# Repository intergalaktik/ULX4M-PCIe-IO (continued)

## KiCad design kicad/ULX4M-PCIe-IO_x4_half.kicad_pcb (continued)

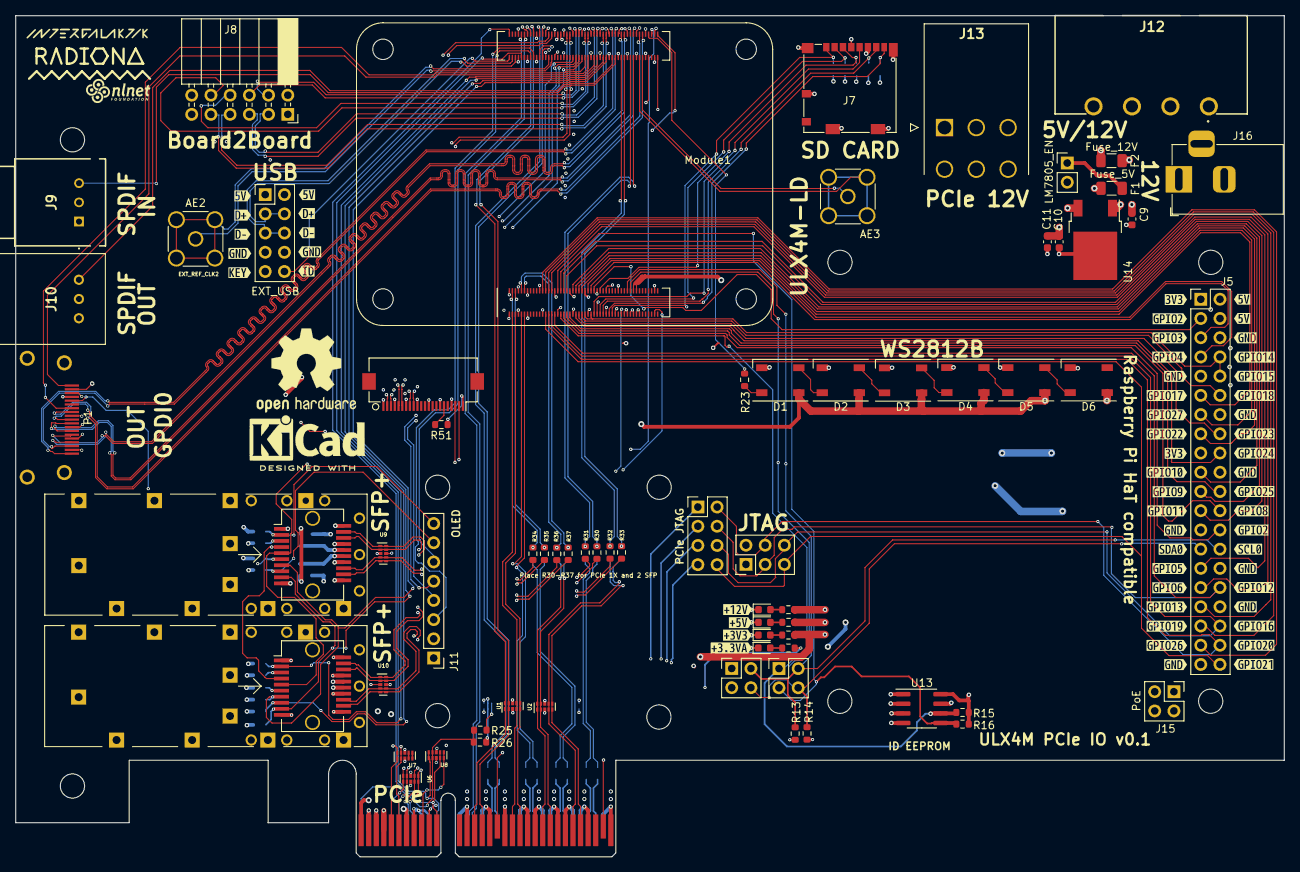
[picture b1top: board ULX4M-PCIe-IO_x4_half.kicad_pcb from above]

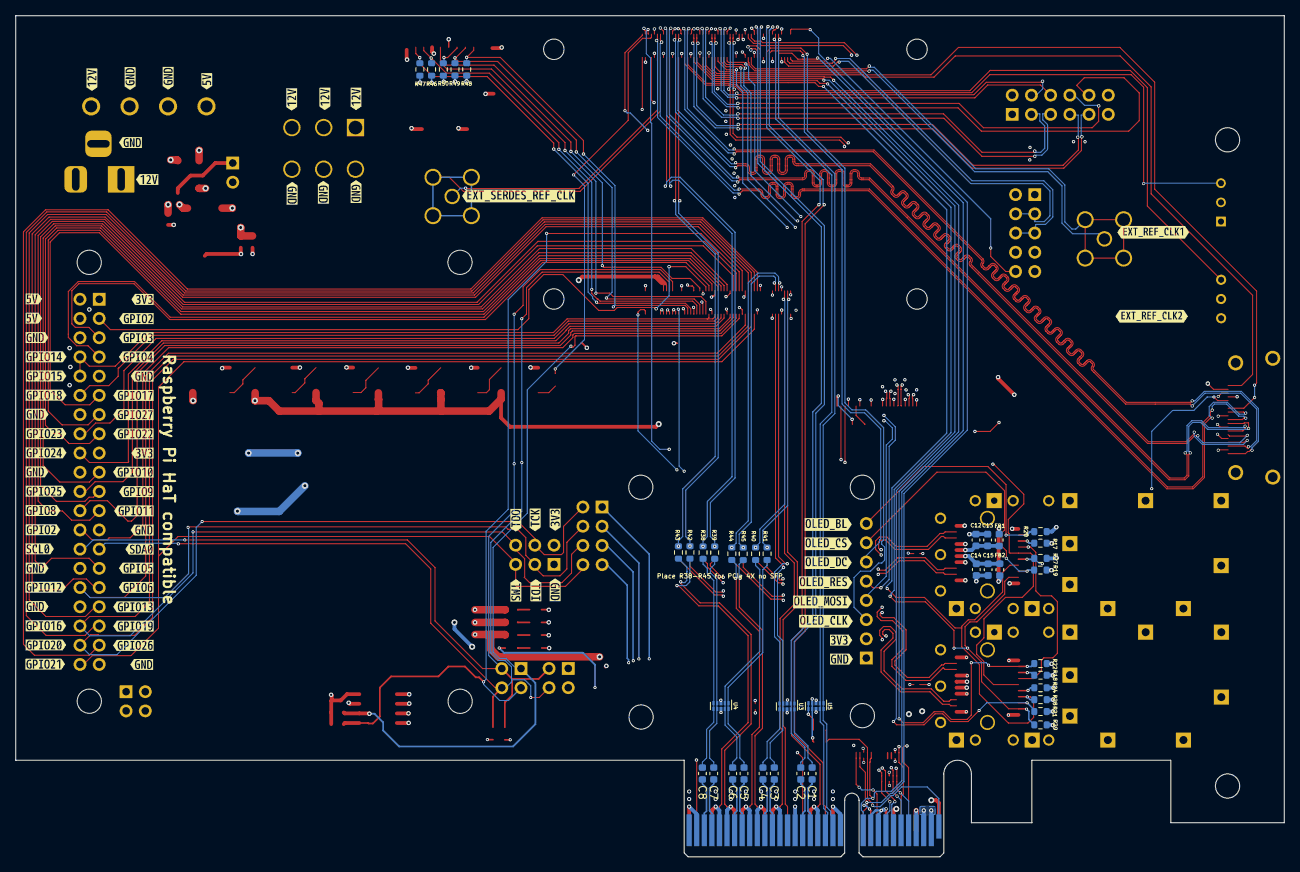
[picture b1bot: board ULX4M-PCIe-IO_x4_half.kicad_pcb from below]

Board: 6 copper layers, 167.7 x 111.2 mm, 241 parts (109 on the bottom side), 161 nets.

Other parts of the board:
kibuzzard-66C31A8D: G***; kibuzzard-66C31A8D
kibuzzard-66C31AAA: G***; kibuzzard-66C31AAA
kibuzzard-63524D1: G***; kibuzzard-63524D95
kibuzzard-63524E7F12: G***; kibuzzard-63524E7F
kibuzzard-63524EC5: G***; kibuzzard-63524EC5
kibuzzard-63524ECE: G***; kibuzzard-63524ECE
kibuzzard-63524ED4: G***; kibuzzard-63524ED4
kibuzzard-63524EDC: G***; kibuzzard-63524EDC
kibuzzard-63524EE2: G***; kibuzzard-63524EE2
kibuzzard-63524EEA: G***; kibuzzard-63524EEA
kibuzzard-63524EF7: G***; kibuzzard-63524EF7
kibuzzard-63524EFF: G***; kibuzzard-63524EFF
kibuzzard-63524F4A: G***; kibuzzard-63524F4A
kibuzzard-63524F4F: G***; kibuzzard-63524F4F
kibuzzard-63524F5B: G***; kibuzzard-63524F5B
kibuzzard-63524F6E: G***; kibuzzard-63524F6E
kibuzzard-63524F8C: G***; kibuzzard-63524F8C
kibuzzard-63524F9F: G***; kibuzzard-63524F9F
kibuzzard-63524F11: G***; kibuzzard-63524F11
kibuzzard-63524F17: G***; kibuzzard-63524F17
kibuzzard-63524F21: G***; kibuzzard-63524F21
kibuzzard-63524F28: G***; kibuzzard-63524F28
kibuzzard-63524F31: G***; kibuzzard-63524F31
kibuzzard-63524F38: G***; kibuzzard-63524F38
kibuzzard-63524F40: G***; kibuzzard-63524F40
kibuzzard-63524F45: G***; kibuzzard-63524F45
kibuzzard-63524F57: G***; kibuzzard-63524F57
kibuzzard-63524F60: G***; kibuzzard-63524F60
kibuzzard-63524F75: G***; kibuzzard-63524F75
kibuzzard-63524F84: G***; kibuzzard-63524F84
kibuzzard-63524F92: G***; kibuzzard-63524F92
kibuzzard-63524F99: G***; kibuzzard-63524F99
kibuzzard-63524FA8: G***; kibuzzard-63524FA8
kibuzzard-63524FAF: G***; kibuzzard-63524FAF
kibuzzard-63524FB4: G***; kibuzzard-63524FB4
kibuzzard-63524FBB: G***; kibuzzard-63524FBB
kibuzzard-63524FC2: G***; kibuzzard-63524FC2
kibuzzard-63524FC9: G***; kibuzzard-63524FC9
kibuzzard-63524FCF: G***; kibuzzard-63524FCF
kibuzzard-63524FD4: G***; kibuzzard-63524FD4
kibuzzard-63524FDC: G***; kibuzzard-63524FDC
kibuzzard-63524FE4: G***; kibuzzard-63524FE4
kibuzzard-63525A7A: G***; kibuzzard-63525A7A
kibuzzard-63525A8D: G***; kibuzzard-63525A8D
kibuzzard-63525A73: G***; kibuzzard-63525A73
kibuzzard-63525A80: G***; kibuzzard-63525A80
kibuzzard-63525A86: G***; kibuzzard-63525A86
kibuzzard-63525A94: G***; kibuzzard-63525A94
kibuzzard-63525AA1: G***; kibuzzard-63525AA1
kibuzzard-63525AA7: G***; kibuzzard-63525AA7
kibuzzard-63525BEB: G***; kibuzzard-63525BEB
kibuzzard-63525C1D: G***; kibuzzard-63525C1D
kibuzzard-63525C11: G***; kibuzzard-63525C11
kibuzzard-63525C35: G***; kibuzzard-63525C35
kibuzzard-63525FEA: G***; kibuzzard-63525FEA
kibuzzard-635253B6: G***; kibuzzard-635253B6
kibuzzard-635253BD: G***; kibuzzard-635253BD
kibuzzard-635253C7: G***; kibuzzard-635253C7
kibuzzard-635253DB: G***; kibuzzard-635253DB
kibuzzard-635253E6: G***; kibuzzard-635253E6
kibuzzard-635253EF: G***; kibuzzard-635253EF
kibuzzard-635253F9: G***; kibuzzard-635253F9
kibuzzard-635254E9: G***; kibuzzard-635254E9
kibuzzard-635254FF: G***; kibuzzard-635254FF
kibuzzard-635255A4: G***; kibuzzard-635255A4
kibuzzard-635255AB: G***; kibuzzard-635255AB
kibuzzard-635256A7: G***; kibuzzard-635256A7
kibuzzard-635256BE: G***; kibuzzard-635256BE
kibuzzard-635256C7: G***; kibuzzard-635256C7
kibuzzard-635256D0: G***; kibuzzard-635256D0
kibuzzard-635256DB: G***; kibuzzard-635256DB
kibuzzard-635669BB: G***; kibuzzard-635669BB
kibuzzard-6352538D: G***; kibuzzard-6352538D
kibuzzard-6352539E: G***; kibuzzard-6352539E
kibuzzard-6352540A: G***; kibuzzard-6352540A
kibuzzard-6352542E: G***; kibuzzard-6352542E
kibuzzard-6352550F: G***; kibuzzard-6352550F
kibuzzard-6352551E: G***; kibuzzard-6352551E
kibuzzard-6352553D: G***; kibuzzard-6352553D
kibuzzard-6352554A: G***; kibuzzard-6352554A
kibuzzard-6352557B: G***; kibuzzard-6352557B
kibuzzard-6352559E: G***; kibuzzard-6352559E
kibuzzard-6352571C, kibuzzard-6352571C#2, kibuzzard-6352571C#3, kibuzzard-6352571C#4, kibuzzard-6352571C#5, kibuzzard-6352571C#6: G***; kibuzzard-6352571C
kibuzzard-6352575D: G***; kibuzzard-6352575D
kibuzzard-6352604E: G***; kibuzzard-6352604E
kibuzzard-6352607D: G***; kibuzzard-6352607D
kibuzzard-6352608E: G***; kibuzzard-6352608E
kibuzzard-6352880A: G***; kibuzzard-6352880A
kibuzzard-63525329: G***; kibuzzard-63525329
kibuzzard-63525356: G***; kibuzzard-63525356
kibuzzard-63525372: G***; kibuzzard-63525372
kibuzzard-63525383: G***; kibuzzard-63525383
kibuzzard-63525395: G***; kibuzzard-63525395
kibuzzard-63525401: G***; kibuzzard-63525401
kibuzzard-63525414: G***; kibuzzard-63525414
kibuzzard-63525426: G***; kibuzzard-63525426
kibuzzard-63525437, kibuzzard-63525437#2: G***; kibuzzard-63525437
kibuzzard-63525509: G***; kibuzzard-63525509
kibuzzard-63525515: G***; kibuzzard-63525515
kibuzzard-63525524: G***; kibuzzard-63525524
kibuzzard-63525536: G***; kibuzzard-63525536
kibuzzard-63525544: G***; kibuzzard-63525544
kibuzzard-63525576: G***; kibuzzard-63525576
kibuzzard-63525581: G***; kibuzzard-63525581
kibuzzard-63525588: G***; kibuzzard-63525588
kibuzzard-63525590: G***; kibuzzard-63525590
kibuzzard-63525598: G***; kibuzzard-63525598
kibuzzard-63525733, kibuzzard-63525733#2, kibuzzard-63525733#3, kibuzzard-63525733#4, kibuzzard-63525733#5: G***; kibuzzard-63525733
kibuzzard-63526015: G***; kibuzzard-63526015
kibuzzard-63526058: G***; kibuzzard-63526058
kibuzzard-63526060: G***; kibuzzard-63526060
kibuzzard-63526086: G***; kibuzzard-63526086
kibuzzard-63526396: G***; kibuzzard-63526396
radiona: radiona

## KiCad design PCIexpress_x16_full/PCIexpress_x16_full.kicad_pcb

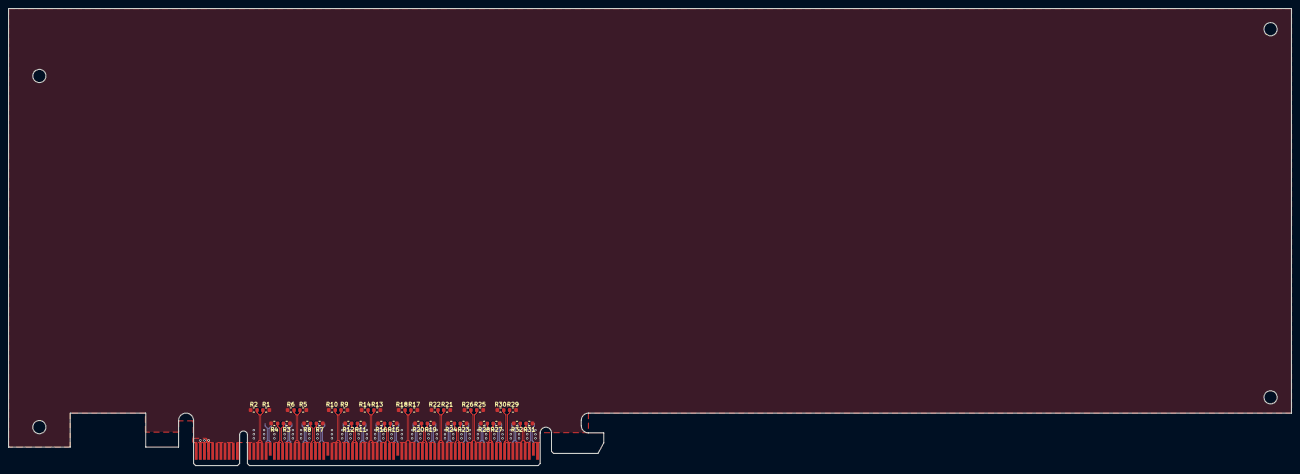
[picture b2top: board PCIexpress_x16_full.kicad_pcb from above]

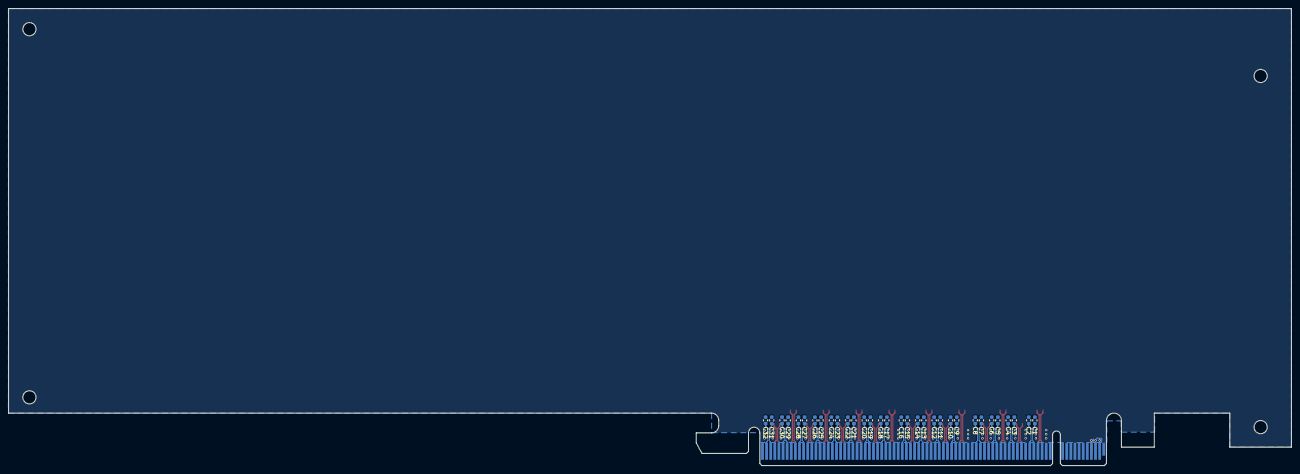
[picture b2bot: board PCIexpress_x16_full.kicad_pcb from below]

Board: 4 copper layers, 312.0 x 111.2 mm, 66 parts (32 on the bottom side), 67 nets.

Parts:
C1, C2, C3, C4, C5, C6, C7, C8, C9, C10, C11, C12, C13, C14, C15, C16, C17, C18, C19, C20, C21, C22, C23, C24, C25, C26, C27, C28, C29, C30, C31, C32: 100n; C_0603_1608Metric
J1: PCIexpress_bracket; PCIexpress_bracket_full
J2: PCIexpress_x16
R1, R2, R3, R4, R5, R6, R7, R8, R9, R10, R11, R12, R13, R14, R15, R16, R17, R18, R19, R20, R21, R22, R23, R24, R25, R26, R27, R28, R29, R30, R31, R32: 49.9; R_0603_1608Metric

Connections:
+3V3: J2.A9, J2.A10, J2.B8
+12V: J2.A2, J2.A3, J2.B1, J2.B2, J2.B3
/PCIexpress_connector/_PER0_N: C2.1, J2.A17
/PCIexpress_connector/_PER0_P: C1.2, J2.A16
/PCIexpress_connector/_PER1_N: C4.1, J2.A22
/PCIexpress_connector/_PER1_P: C3.2, J2.A21
/PCIexpress_connector/_PER2_N: C6.1, J2.A26
/PCIexpress_connector/_PER2_P: C5.2, J2.A25
/PCIexpress_connector/_PER3_N: C8.1, J2.A30
/PCIexpress_connector/_PER3_P: C7.2, J2.A29
/PCIexpress_connector/_PER4_N: C10.1, J2.A36
/PCIexpress_connector/_PER4_P: C9.2, J2.A35
/PCIexpress_connector/_PER5_N: C12.1, J2.A40
/PCIexpress_connector/_PER5_P: C11.2, J2.A39
/PCIexpress_connector/_PER6_N: C14.1, J2.A44
/PCIexpress_connector/_PER6_P: C13.2, J2.A43
/PCIexpress_connector/_PER7_N: C16.1, J2.A48
/PCIexpress_connector/_PER7_P: C15.2, J2.A47
/PCIexpress_connector/_PER8_N: C18.1, J2.A53
/PCIexpress_connector/_PER8_P: C17.2, J2.A52
/PCIexpress_connector/_PER9_N: C20.1, J2.A57
/PCIexpress_connector/_PER9_P: C19.2, J2.A56
/PCIexpress_connector/_PER10_N: C22.1, J2.A61
/PCIexpress_connector/_PER10_P: C21.2, J2.A60
/PCIexpress_connector/_PER11_N: C24.1, J2.A65
/PCIexpress_connector/_PER11_P: C23.2, J2.A64
/PCIexpress_connector/_PER12_N: C26.1, J2.A69
/PCIexpress_connector/_PER12_P: C25.2, J2.A68
/PCIexpress_connector/_PER13_N: C28.1, J2.A73
/PCIexpress_connector/_PER13_P: C27.2, J2.A72
/PCIexpress_connector/_PER14_N: C30.1, J2.A77
/PCIexpress_connector/_PER14_P: C29.2, J2.A76
/PCIexpress_connector/_PER15_N: C32.1, J2.A81
/PCIexpress_connector/_PER15_P: C31.2, J2.A80
/PET0_N: J2.B15, R1.1
/PET0_P: J2.B14, R2.1
/PET1_N: J2.B20, R3.1
/PET1_P: J2.B19, R4.1
/PET2_N: J2.B24, R5.1
/PET2_P: J2.B23, R6.1
/PET3_N: J2.B28, R7.1
/PET3_P: J2.B27, R8.1
/PET4_N: J2.B34, R9.1
/PET4_P: J2.B33, R10.1
/PET5_N: J2.B38, R11.1
/PET5_P: J2.B37, R12.1
/PET6_N: J2.B42, R13.1
/PET6_P: J2.B41, R14.1
/PET7_N: J2.B46, R15.1
/PET7_P: J2.B45, R16.1
/PET8_N: J2.B51, R17.1
/PET8_P: J2.B50, R18.1
/PET9_N: J2.B55, R19.1
/PET9_P: J2.B54, R20.1
/PET10_N: J2.B59, R21.1
/PET10_P: J2.B58, R22.1
/PET11_N: J2.B63, R23.1
/PET11_P: J2.B62, R24.1
/PET12_N: J2.B67, R25.1
/PET12_P: J2.B66, R26.1
/PET13_N: J2.B71, R27.1
/PET13_P: J2.B70, R28.1
/PET14_N: J2.B75, R29.1
/PET14_P: J2.B74, R30.1
/PET15_N: J2.B79, R31.1
/PET15_P: J2.B78, R32.1
GND: J2.A4, J2.A12, J2.A15, J2.A18, J2.A20, J2.A23, J2.A24, J2.A27, J2.A28, J2.A31, J2.A34, J2.A37, J2.A38, J2.A41, J2.A42, J2.A45, J2.A46, J2.A49, J2.A51, J2.A54, J2.A55, J2.A58, J2.A59, J2.A62, J2.A63, J2.A66, J2.A67, J2.A70, J2.A71, J2.A74, J2.A75, J2.A78, J2.A79, J2.A82, J2.B4, J2.B7, J2.B13, J2.B16, J2.B18, J2.B21, J2.B22, J2.B25, J2.B26, J2.B29, J2.B32, J2.B35, J2.B36, J2.B39, J2.B40, J2.B43, J2.B44, J2.B47, J2.B49, J2.B52, J2.B53, J2.B56, J2.B57, J2.B60, J2.B61, J2.B64, J2.B65, J2.B68, J2.B69, J2.B72, J2.B73, J2.B76, J2.B77, J2.B80, R1.2, R2.2, R3.2, R4.2, R5.2, R6.2, R7.2, R8.2, R9.2, R10.2, R11.2, R12.2, R13.2, R14.2, R15.2, R16.2, R17.2, R18.2, R19.2, R20.2, R21.2, R22.2, R23.2, R24.2, R25.2, R26.2, R27.2, R28.2, R29.2, R30.2, R31.2, R32.2

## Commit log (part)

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2022-10-10 Cleanup
2022-10-12 Renaming all files fix #7
2022-10-12 Modules update
2022-10-12 Schematics change
2022-10-12 Moving symbol and footprint to lib folder
2022-10-12 Adding SPDIF
2022-10-12 Update connector
2022-10-13 Readme update
2022-10-13 Adding picture and reference boards
2022-10-15 Adding PCIe power connector - fix 31
2022-10-15 Adding logos and version text fix #3 fix #24
2022-10-15 Adding LEDs fix #4
2022-10-20 Adding more features
2022-10-20 Adding new 3D kicad render
2022-10-20 Adding barrel connector, adding JTAG, adding new pic
2022-10-20 Connecting GPIO, GPDI, B2B, SD
2022-10-20 Adding more connections - adding SFP parts
2022-10-21 Adding more descrition to PCB pins
2022-10-24 finalising connections
2022-10-24 Routing PCIe
2022-10-25 Routing GPIOs
2022-10-25 Routing B2B
2022-10-26 Routing all pins from CM4 connector
2022-10-27 Routing all gpio
2022-10-27 Routing
2022-10-28 Adding blender render image
2024-08-07 Connected most of the lines. Fixed some deformed lines also.
2024-08-07 Added backups.
2024-08-21 Fixing errors - adding length match
2025-04-09 dodani okviri na shemi
2025-04-09 uređeni okviri postavljeni u format A3
2025-04-10 uređivanje sheme
2025-04-10 uređena schema
2025-04-15 dodan pdf
